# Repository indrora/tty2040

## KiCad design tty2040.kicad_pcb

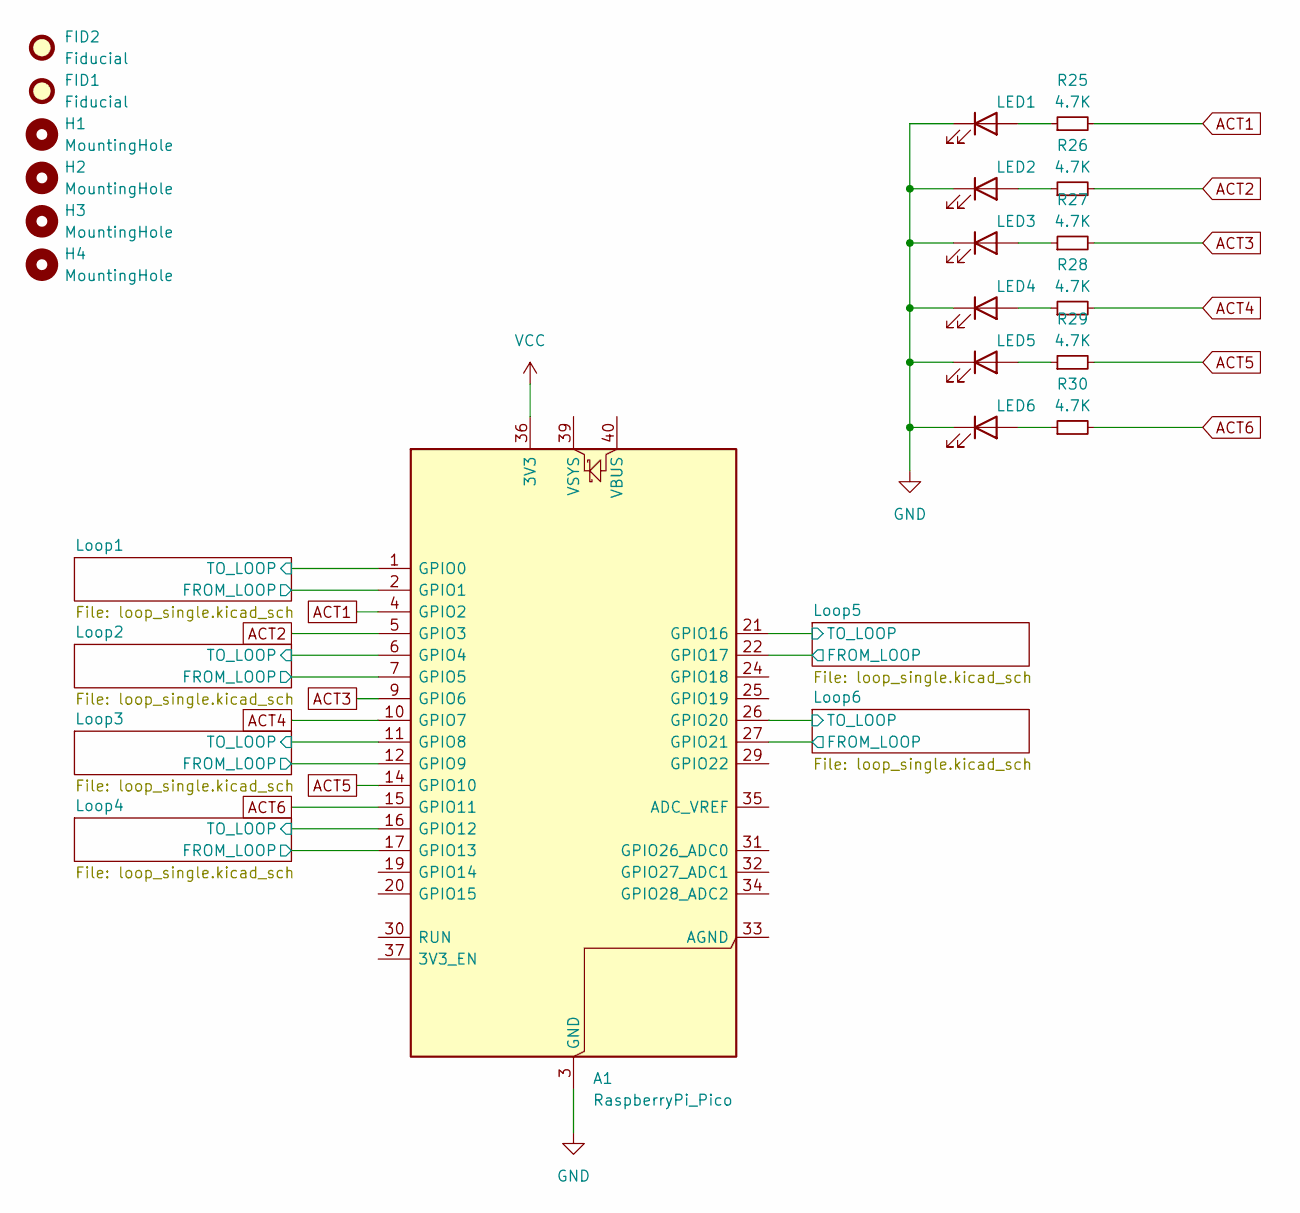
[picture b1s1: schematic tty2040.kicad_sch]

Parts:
A1: RaspberryPi_Pico; RaspberryPi_Pico_Common
FID1, FID2: Fiducial; Fiducial_1mm_Mask3mm
H1, H2, H3, H4: MountingHole; MountingHole_2.7mm_M2.5
LED1: KT-0603R; LED_D3.0mm
LED2, LED3, LED4, LED5, LED6: KT-0603R; LED_D3.0mm; LCSC Part C2297
R25, R26, R27, R28, R29, R30: 4.7K; R_Axial_DIN0204_L3.6mm_D1.6mm_P7.62mm_Horizontal; LCSC C17673

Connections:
/Loop1/FROM_LOOP: A1.2 (GPIO1); also elsewhere on the board
/Loop1/TO_LOOP: A1.1 (GPIO0); also elsewhere on the board
/Loop2/FROM_LOOP: A1.7 (GPIO5); also elsewhere on the board
/Loop2/TO_LOOP: A1.6 (GPIO4); also elsewhere on the board
/Loop3/FROM_LOOP: A1.12 (GPIO9); also elsewhere on the board
/Loop3/TO_LOOP: A1.11 (GPIO8); also elsewhere on the board
/Loop4/FROM_LOOP: A1.17 (GPIO13); also elsewhere on the board
/Loop4/TO_LOOP: A1.16 (GPIO12); also elsewhere on the board
/Loop5/FROM_LOOP: A1.22 (GPIO17); also elsewhere on the board
/Loop5/TO_LOOP: A1.21 (GPIO16); also elsewhere on the board
/Loop6/FROM_LOOP: A1.27 (GPIO21); also elsewhere on the board
/Loop6/TO_LOOP: A1.26 (GPIO20); also elsewhere on the board
ACT1: A1.4 (GPIO2), R25.2
ACT2: A1.5 (GPIO3), R26.2
ACT3: A1.9 (GPIO6), R27.2
ACT4: A1.10 (GPIO7), R28.2
ACT5: A1.14 (GPIO10), R29.2
ACT6: A1.15 (GPIO11), R30.2
GND: A1.3 (GND), A1.8 (GND), A1.13 (GND), A1.18 (GND), A1.23 (GND), A1.28 (GND), A1.38 (GND), LED1.1 (K), LED2.1 (K), LED3.1 (K), LED4.1 (K), LED5.1 (K), LED6.1 (K); also elsewhere on the board
unnamed: LED1.2 (A), R25.1
unnamed: LED2.2 (A), R26.1
unnamed: LED3.2 (A), R27.1
unnamed: LED4.2 (A), R28.1
unnamed: LED5.2 (A), R29.1
unnamed: LED6.2 (A), R30.1
VCC: A1.36 (3V3); also elsewhere on the board

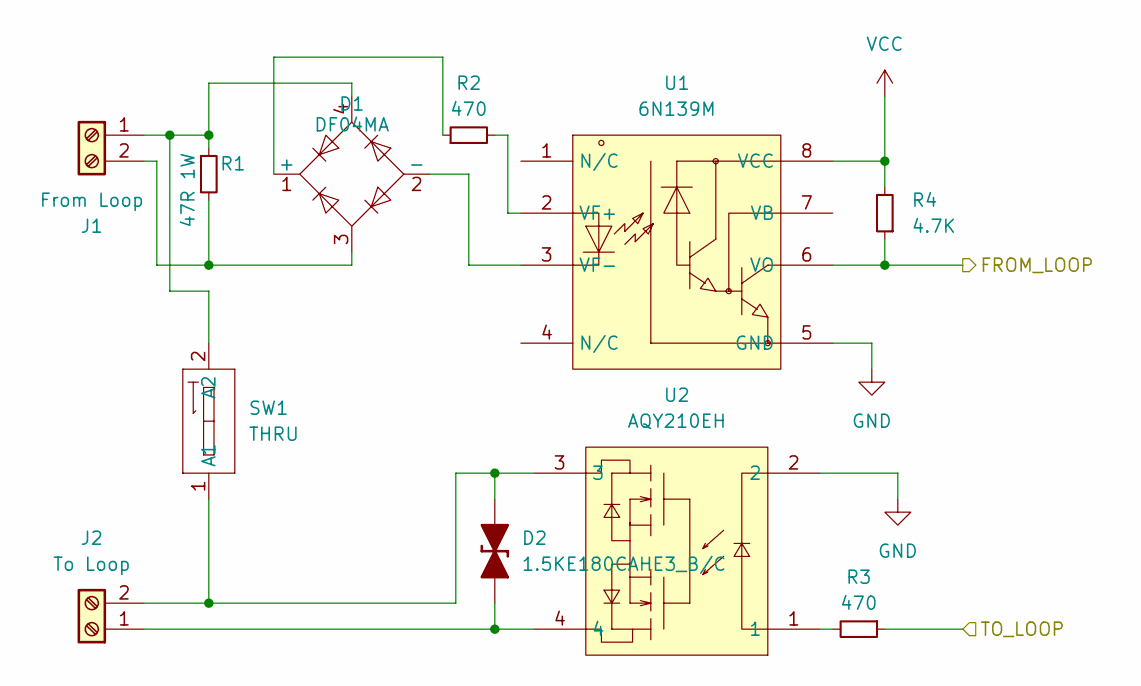
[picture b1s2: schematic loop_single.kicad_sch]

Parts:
D1: DF04MA; Diode_Bridge_DIP-4_W7.62mm_P5.08mm; Mouser 625-DF04MA-E3
D2: 1.5KE180CAHE3_B/C; D_A-405_P10.16mm_Horizontal; LCSC Part C519810
J1: From Loop; TerminalBlock_5mm_labeled; LCSC C2997275
J2: To Loop; TerminalBlock_5mm_labeled; LCSC C2997275
R1: 47R 1W; R_Axial_DIN0309_L9.0mm_D3.2mm_P12.70mm_Horizontal; LCSC C341654
R2, R3: 470; R_Axial_DIN0204_L3.6mm_D1.6mm_P7.62mm_Horizontal; LCSC C17710
R4: 4.7K; R_Axial_DIN0204_L3.6mm_D1.6mm_P7.62mm_Horizontal; LCSC C17673
SW1: THRU; SW_DIP_SPSTx01_Slide_6.7x4.1mm_W7.62mm_P2.54mm_LowProfile; Mouser 490-DS04-254-1S-01BK
U1: 6N139M; DIP-8_W10.16mm; Mouser 512-6N139M
U2: AQY210EH; DIP-4_W7.62mm; Mouser 769-AQY210EH

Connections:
/Loop1/FROM_LOOP: R4.1, U1.6 (VO); also elsewhere on the board
/Loop1/TO_LOOP: R3.1; also elsewhere on the board
GND: U1.5 (GND), U2.2; also elsewhere on the board
unnamed: D1.1 (+), R2.1
unnamed: D1.2 (-), U1.3 (VF-)
unnamed: D2.2 (A), J2.1, U2.4
unnamed: D2.1 (K), J2.2, SW1.1 (A1), U2.3
unnamed: D1.4, J1.1, R1.1, SW1.2 (A2)
unnamed: D1.3, J1.2, R1.2
unnamed: R3.2, U2.1
unnamed: R2.2, U1.2 (VF+)
VCC: R4.2, U1.8 (VCC); also elsewhere on the board

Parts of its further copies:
D3, D5, D7, D9, D11: DF04MA; Diode_Bridge_DIP-4_W7.62mm_P5.08mm; Mouser 625-DF04MA-E3
D13, D15, D16, D17, D18: 1.5KE180CAHE3_B/C; D_A-405_P10.16mm_Horizontal; LCSC Part C519810
J3, J5, J7, J9, J11: From Loop; TerminalBlock_5mm_labeled; LCSC C2997275
J4, J6, J8, J10, J12: To Loop; TerminalBlock_5mm_labeled; LCSC C2997275
R5, R9, R13, R17, R21: 47R 1W; R_Axial_DIN0309_L9.0mm_D3.2mm_P12.70mm_Horizontal; LCSC C341654
R6, R7, R10, R11, R14, R15, R18, R19, R22, R23: 470; R_Axial_DIN0204_L3.6mm_D1.6mm_P7.62mm_Horizontal; LCSC C17710
R8, R12, R16, R20, R24: 4.7K; R_Axial_DIN0204_L3.6mm_D1.6mm_P7.62mm_Horizontal; LCSC C17673
SW2, SW3, SW4, SW5, SW6: THRU; SW_DIP_SPSTx01_Slide_6.7x4.1mm_W7.62mm_P2.54mm_LowProfile; Mouser 490-DS04-254-1S-01BK
U3, U5, U7, U9, U11: 6N139M; DIP-8_W10.16mm; Mouser 512-6N139M
U4, U6, U8, U10, U12: AQY210EH; DIP-4_W7.62mm; Mouser 769-AQY210EH

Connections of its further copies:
/Loop2/FROM_LOOP: R8.1, U3.6 (VO); also elsewhere on the board
/Loop2/TO_LOOP: R7.1; also elsewhere on the board
/Loop3/FROM_LOOP: R12.1, U5.6 (VO); also elsewhere on the board
/Loop3/TO_LOOP: R11.1; also elsewhere on the board
/Loop4/FROM_LOOP: R16.1, U7.6 (VO); also elsewhere on the board
/Loop4/TO_LOOP: R15.1; also elsewhere on the board
/Loop5/FROM_LOOP: R20.1, U9.6 (VO); also elsewhere on the board
/Loop5/TO_LOOP: R19.1; also elsewhere on the board
/Loop6/FROM_LOOP: R24.1, U11.6 (VO); also elsewhere on the board
/Loop6/TO_LOOP: R23.1; also elsewhere on the board
GND: U3.5 (GND), U4.2, U5.5 (GND), U6.2, U7.5 (GND), U8.2, U9.5 (GND), U10.2, U11.5 (GND), U12.2; also elsewhere on the board
unnamed: D3.1 (+), R6.1
unnamed: D3.2 (-), U3.3 (VF-)
unnamed: D5.1 (+), R10.1
unnamed: D5.2 (-), U5.3 (VF-)
unnamed: D7.1 (+), R14.1
unnamed: D7.2 (-), U7.3 (VF-)
unnamed: D9.1 (+), R18.1
unnamed: D9.2 (-), U9.3 (VF-)
unnamed: D11.1 (+), R22.1
unnamed: D11.2 (-), U11.3 (VF-)
unnamed: D3.4, J3.1, R5.1, SW2.2 (A2)
unnamed: D3.3, J3.2, R5.2
unnamed: D13.2 (A), J4.1, U4.4
unnamed: D13.1 (K), J4.2, SW2.1 (A1), U4.3
unnamed: D5.4, J5.1, R9.1, SW3.2 (A2)
unnamed: D5.3, J5.2, R9.2
unnamed: D15.2 (A), J6.1, U6.4
unnamed: D15.1 (K), J6.2, SW3.1 (A1), U6.3
unnamed: D7.4, J7.1, R13.1, SW4.2 (A2)
unnamed: D7.3, J7.2, R13.2
unnamed: D16.2 (A), J8.1, U8.4
unnamed: D16.1 (K), J8.2, SW4.1 (A1), U8.3
unnamed: D9.4, J9.1, R17.1, SW5.2 (A2)
unnamed: D9.3, J9.2, R17.2
unnamed: D17.2 (A), J10.1, U10.4
unnamed: D17.1 (K), J10.2, SW5.1 (A1), U10.3
unnamed: D11.4, J11.1, R21.1, SW6.2 (A2)
unnamed: D11.3, J11.2, R21.2
unnamed: D18.2 (A), J12.1, U12.4
unnamed: D18.1 (K), J12.2, SW6.1 (A1), U12.3
unnamed: R7.2, U4.1
unnamed: R11.2, U6.1
unnamed: R15.2, U8.1
unnamed: R19.2, U10.1
unnamed: R23.2, U12.1
unnamed: R6.2, U3.2 (VF+)
unnamed: R10.2, U5.2 (VF+)
unnamed: R14.2, U7.2 (VF+)
unnamed: R18.2, U9.2 (VF+)
unnamed: R22.2, U11.2 (VF+)
VCC: R8.2, R12.2, R16.2, R20.2, R24.2, U3.8 (VCC), U5.8 (VCC), U7.8 (VCC), U9.8 (VCC), U11.8 (VCC); also elsewhere on the board

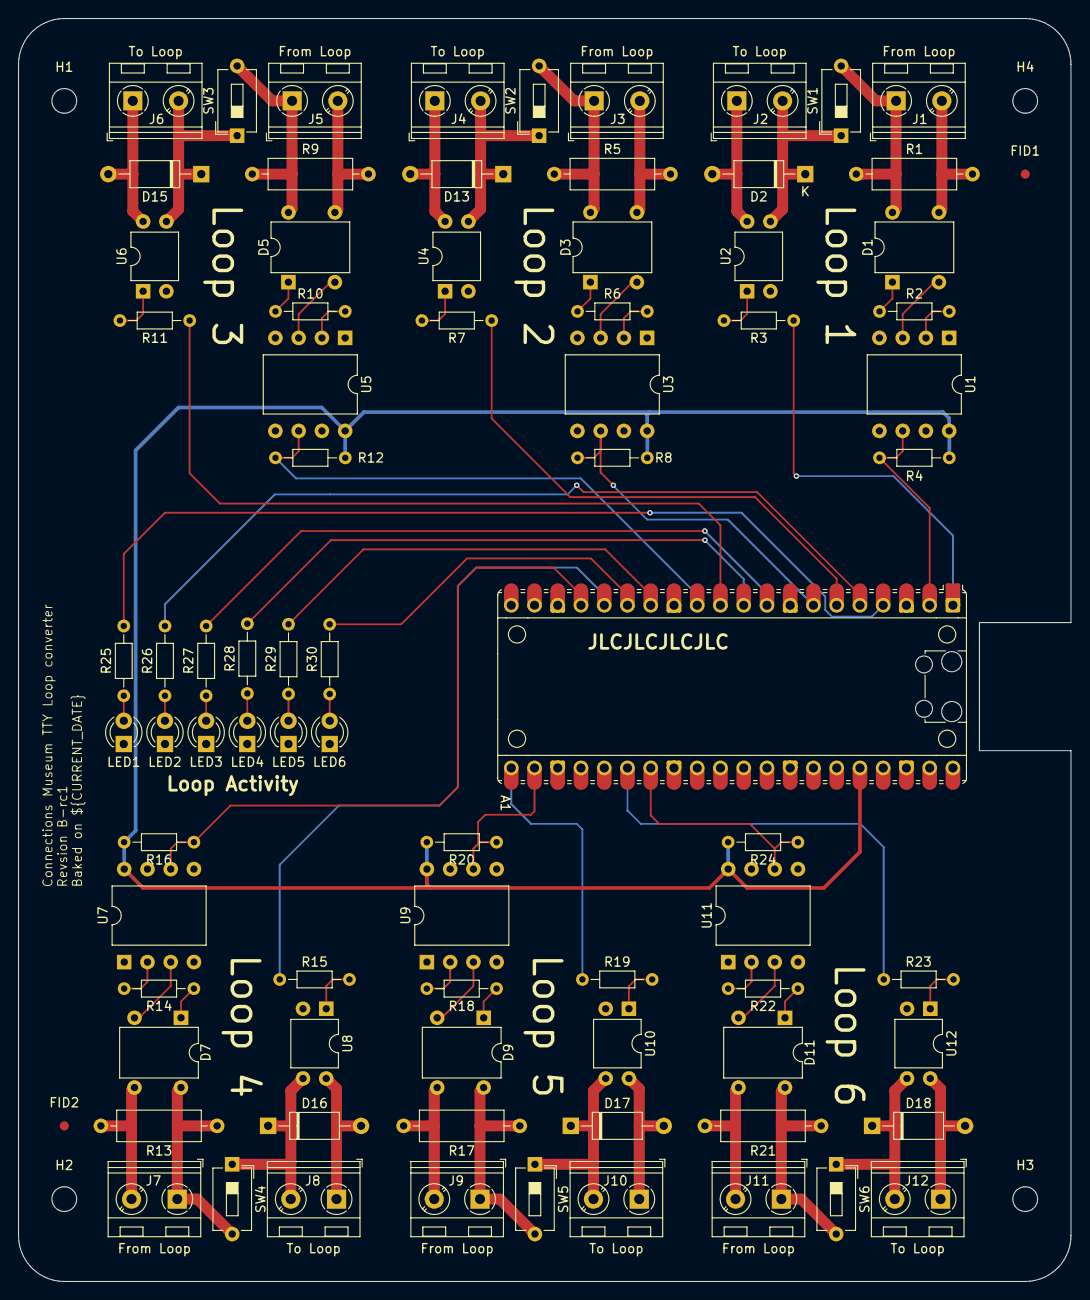
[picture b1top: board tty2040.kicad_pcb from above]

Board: 2 copper layers, 115.0 x 138.0 mm, 85 parts (0 on the bottom side), 74 nets.

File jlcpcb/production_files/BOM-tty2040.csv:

Comment,Designator,Footprint,LCSC,Quantity
4.7K,"R12,R16,R20,R24,R25,R26,R27,R28,R29,R30,R4,R8",R_Axial_DIN0204_L3.6mm_D1.6mm_P7.62mm_Horizontal,C17673,12
470,"R10,R11,R14,R15,R18,R19,R2,R22,R23,R3,R6,R7",R_Axial_DIN0204_L3.6mm_D1.6mm_P7.62mm_Horizontal,C17710,12
DF04MA,"D1,D11,D3,D5,D7,D9",Diode_Bridge_DIP-4_W7.62mm_P5.08mm,C193012,6
KT-0603R,"LED2,LED3,LED4,LED5,LED6",LED_D3.0mm,C2297,5
From Loop,"J1,J10,J11,J12,J2,J3,J4,J5,J6,J7,J8,J9",TerminalBlock_5mm_labeled,C2997275,12
47R 1W,"R1,R13,R17,R21,R5,R9",R_Axial_DIN0309_L9.0mm_D3.2mm_P12.70mm_Horizontal,C341654,6
1.5KE180CAHE3_B/C,"D13,D15,D16,D17,D18,D2",D_A-405_P10.16mm_Horizontal,C519810,6
6N139M,U3,DIP-8_W10.16mm,,1
THRU,SW1,SW_DIP_SPSTx01_Slide_6.7x4.1mm_W7.62mm_P2.54mm_LowProfile,,1
THRU,SW4,SW_DIP_SPSTx01_Slide_6.7x4.1mm_W7.62mm_P2.54mm_LowProfile,,1
6N139M,U9,DIP-8_W10.16mm,,1
6N139M,U7,DIP-8_W10.16mm,,1
AQY210EH,U8,DIP-4_W7.62mm,,1
6N139M,U5,DIP-8_W10.16mm,,1
AQY210EH,U4,DIP-4_W7.62mm,,1
THRU,SW2,SW_DIP_SPSTx01_Slide_6.7x4.1mm_W7.62mm_P2.54mm_LowProfile,,1
AQY210EH,U6,DIP-4_W7.62mm,,1
AQY210EH,U10,DIP-4_W7.62mm,,1
6N139M,U1,DIP-8_W10.16mm,,1
THRU,SW3,SW_DIP_SPSTx01_Slide_6.7x4.1mm_W7.62mm_P2.54mm_LowProfile,,1
THRU,SW5,SW_DIP_SPSTx01_Slide_6.7x4.1mm_W7.62mm_P2.54mm_LowProfile,,1
AQY210EH,U12,DIP-4_W7.62mm,,1
THRU,SW6,SW_DIP_SPSTx01_Slide_6.7x4.1mm_W7.62mm_P2.54mm_LowProfile,,1
KT-0603R,LED1,LED_D3.0mm,,1
6N139M,U11,DIP-8_W10.16mm,,1
AQY210EH,U2,DIP-4_W7.62mm,,1
RaspberryPi_Pico,A1,RaspberryPi_Pico_Common,,1

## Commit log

2025-02-09 wololo
2025-02-20 rev a ready for go
2025-03-03 Initial gerbers (has issues)
2025-03-03 Rev b begin
2025-03-05 revB continue routing
2025-03-11 new gitignore entries
2025-03-11 Thru-Hole version a go-go
2025-03-11 rev B thru-hole prod
